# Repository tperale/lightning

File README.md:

# lightning

More to come soon ...

## Breakout board

Breakout board design for the AS3935 lightning and storm sensor based on the [embeddedadventures.com](https://www.embeddedadventures.com/as3935_lightning_sensor_module_mod-1016.html) breakout board design.

### BOM

| Ref | Qty | Value | Packaging |
|----|---|-------|---------------------------------------|
| C3 | 1 | 10uF  | Capacitors_SMD:C_1206_HandSoldering   |
| C1 | 1 | 270pF | Capacitors_SMD:C_1206_HandSoldering   |
| C2 | 1 | 680pF | Capacitors_SMD:C_1206_HandSoldering   |
| C5, C6 | 2 | 1uF | Capacitors_SMD:C_1206_HandSoldering |
| C4 | 1 | 100nF | Capacitors_SMD:C_1206_HandSoldering   |
| L1 | 1 | MA5532-AE | MA5532-AE:MA5532-AE               |
| R1, R3, R2 | 3 | 10k | Resistors_SMD:R_1206_HandSoldering |
| U1 | 1 | AS3935 | Housings_DFN_QFN:QFN-16-1EP_4x4mm_Pitch0.65mm |

### OSHPark

The breakout board is available to order from OSHPark.

<a href="https://oshpark.com/shared_projects/cbE38twI"></img></a>

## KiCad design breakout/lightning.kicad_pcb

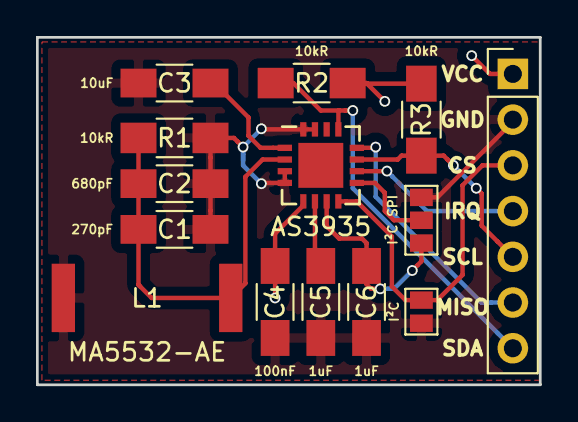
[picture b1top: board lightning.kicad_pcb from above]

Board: 2 copper layers, 27.9 x 19.3 mm, 14 parts (0 on the bottom side), 11 nets.

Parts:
C1: 270pF; C_1206_HandSoldering
C2: 680pF; C_1206_HandSoldering
C3: 10uF; C_1206_HandSoldering
C4: 100nF; C_1206_HandSoldering
C5, C6: 1uF; C_1206_HandSoldering
J1: GS2
J2: GS3
J3: CONN_01X07; Pin_Header_Straight_1x07_Pitch2.54mm
L1: MA5532-AE
R1, R2, R3: 10kR; R_1206_HandSoldering
U1: AS3935; QFN-16-1EP_4x4mm_Pitch0.65mm

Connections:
/CS: J1.2, J3.3, U1.8
/IRQ: J3.4, U1.10
/MISO: J3.6, U1.12
/SCL: J3.5, R3.2, U1.11
/SDA/MOSB: J3.7, R2.2, U1.13
/SI: J2.2, U1.9
GND: C1.2, C2.2, C3.1, C4.2, C5.2, C6.1, J1.1, J2.3, J3.2, L1.2, R1.2, U1.3, U1.4, U1.15, U1.16
unnamed: C1.1, C2.1, L1.1, R1.1, U1.2
unnamed: C3.2, U1.1
unnamed: C5.1, U1.6
VCC: C4.1, C6.2, J2.1, J3.1, R2.1, R3.1, U1.5, U1.7

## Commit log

2017-08-17 [add] First commit
2017-09-16 [add] Matching footprints to components
2017-09-16 [fix] Wrong size pitch for the connectors.
2017-09-16 [enh] Use solder jumper instead of physical one.
2017-09-16 [add] Connections0
2017-09-16 [enh] Logos on board
2017-10-14 [add] BOM to the README
2017-10-22 [add] Add MA5532 datasheet
2017-10-22 [fix] MA5532 footprint
2017-10-23 [enh] Enhance silkscreen indications and traces layout
